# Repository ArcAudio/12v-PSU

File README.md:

# 12v-PSU
PSU

Use v2. Has correct cap traces.

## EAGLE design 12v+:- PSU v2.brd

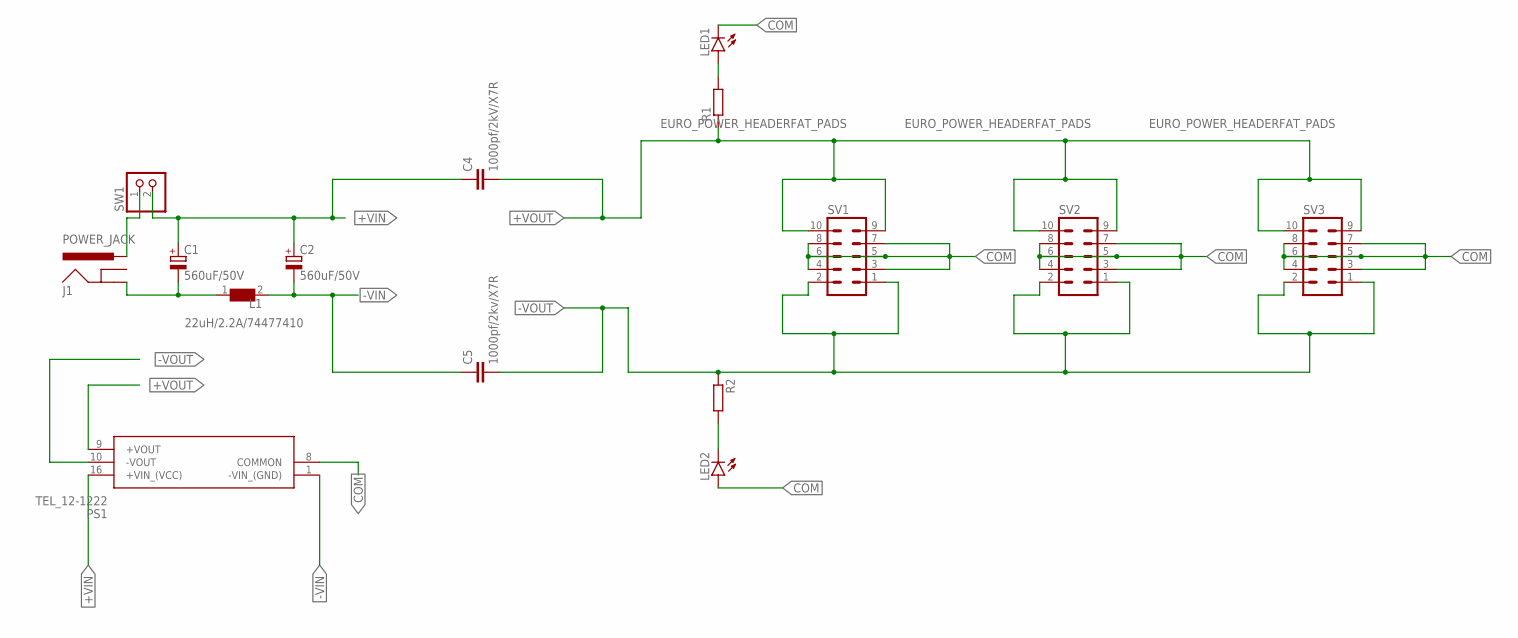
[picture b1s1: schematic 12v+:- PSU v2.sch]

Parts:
C1, C2: 560uF/50V; E7,5-16
C4: 1000pf/2kV/X7R; C1808
C5: 1000pf/2kv/X7R; C1808
J1: POWER_JACK; POWER_JACK_PTH
L1: 22uH/2.2A/74477410; WE-PD2_5848/5820
LED1, LED2: LED3MM
PS1: TEL_12-1222; TEL121222
R1, R2: RESISTOR7MM; 7MM_RESISTOR
SV1, SV2, SV3: EURO_POWER_HEADERFAT_PADS; EURO_PWR_HEADER_FAT
SW1: PINHD-1X2; 1X02

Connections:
+VIN: C1.+, C2.+, C4.1, PS1.16 (+VIN_(VCC)), SW1.2
+VOUT: C4.2, PS1.9 (+VOUT), R1.1, SV1.9, SV1.10, SV2.9, SV2.10, SV3.9, SV3.10
-VIN: C2.-, C5.1, L1.2, PS1.1 (-VIN_(GND))
-VOUT: C5.2, PS1.10 (-VOUT), R2.1, SV1.1, SV1.2, SV2.1, SV2.2, SV3.1, SV3.2
COM: LED1.K (C), LED2.A, PS1.8 (COMMON), SV1.3, SV1.4, SV1.5, SV1.6, SV1.7, SV1.8, SV2.3, SV2.4, SV2.5, SV2.6, SV2.7, SV2.8, SV3.3, SV3.4, SV3.5, SV3.6, SV3.7, SV3.8
unnamed: J1.PWR, SW1.1
unnamed: C1.-, J1.GND, L1.1
unnamed: LED1.A, R1.2
unnamed: LED2.K (C), R2.2

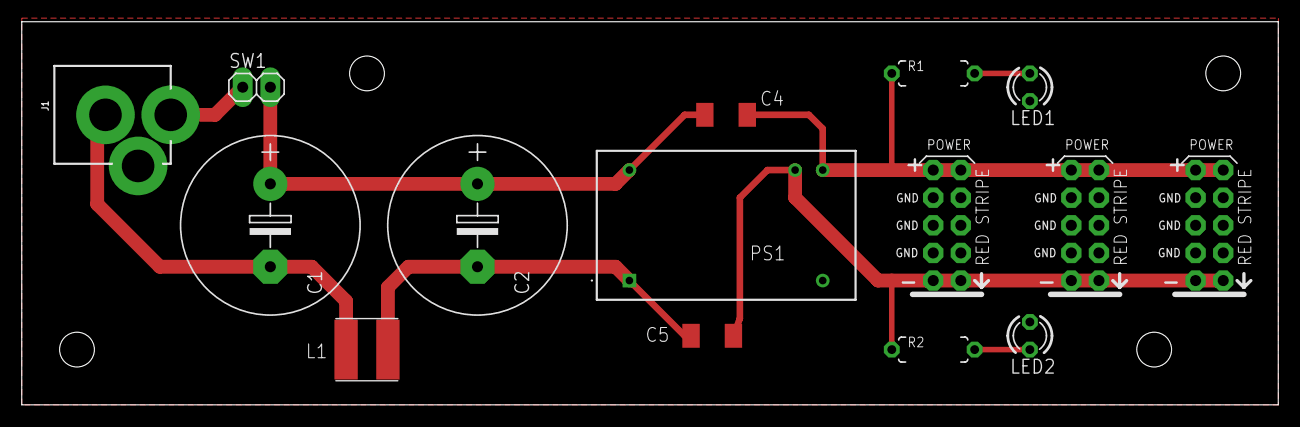
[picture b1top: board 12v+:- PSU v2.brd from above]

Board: 2 copper layers, 115.5 x 35.2 mm, 19 parts (0 on the bottom side), 9 nets.

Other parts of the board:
U$1, U$2, U$3, U$4: MOUNTING_HOLE

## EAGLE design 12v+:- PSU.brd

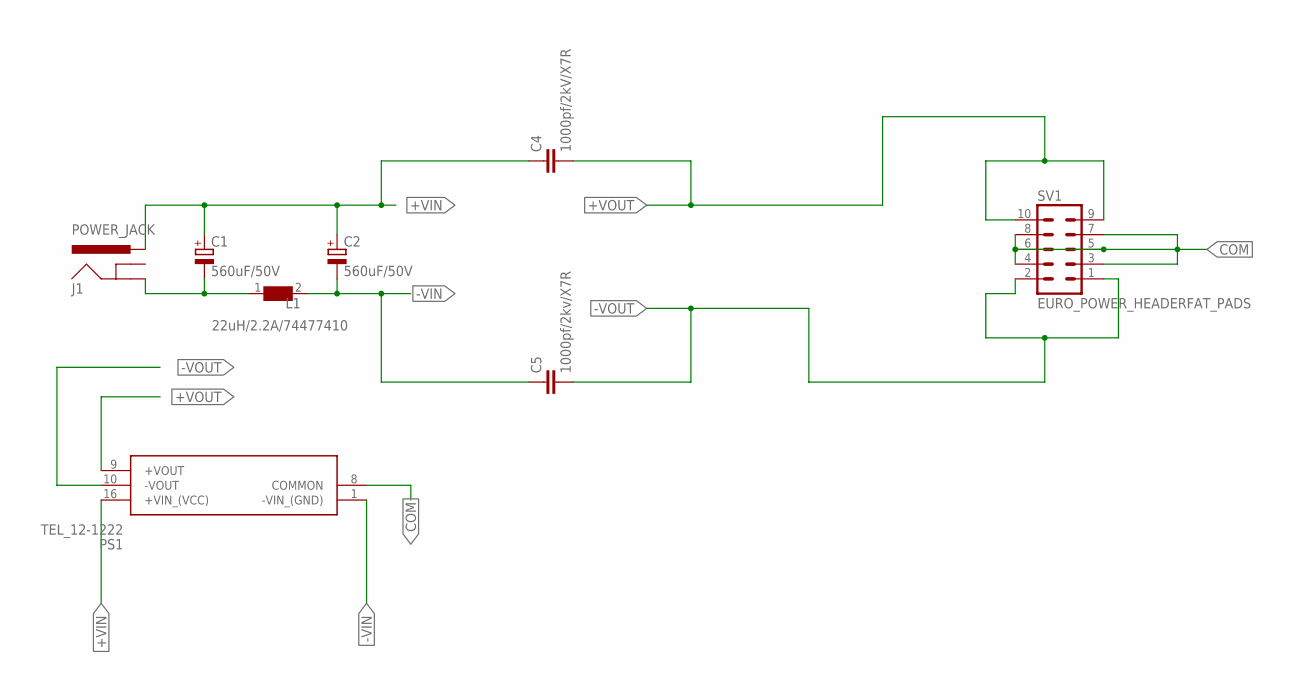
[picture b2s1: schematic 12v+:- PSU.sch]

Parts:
C1, C2: 560uF/50V; E7,5-16
C4: 1000pf/2kV/X7R; C0805
C5: 1000pf/2kv/X7R; C0805
J1: POWER_JACK; POWER_JACK_PTH
L1: 22uH/2.2A/74477410; WE-PD2_5848/5820
PS1: TEL_12-1222; TEL121222
SV1: EURO_POWER_HEADERFAT_PADS; EURO_PWR_HEADER_FAT

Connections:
+VIN: C1.+, C2.+, C4.1, J1.PWR, PS1.16 (+VIN_(VCC))
+VOUT: C4.2, PS1.9 (+VOUT), SV1.9, SV1.10
-VIN: C2.-, C5.1, L1.2, PS1.1 (-VIN_(GND))
-VOUT: C5.2, PS1.10 (-VOUT), SV1.1, SV1.2
COM: PS1.8 (COMMON), SV1.3, SV1.4, SV1.5, SV1.6, SV1.7, SV1.8
unnamed: C1.-, J1.GND, L1.1

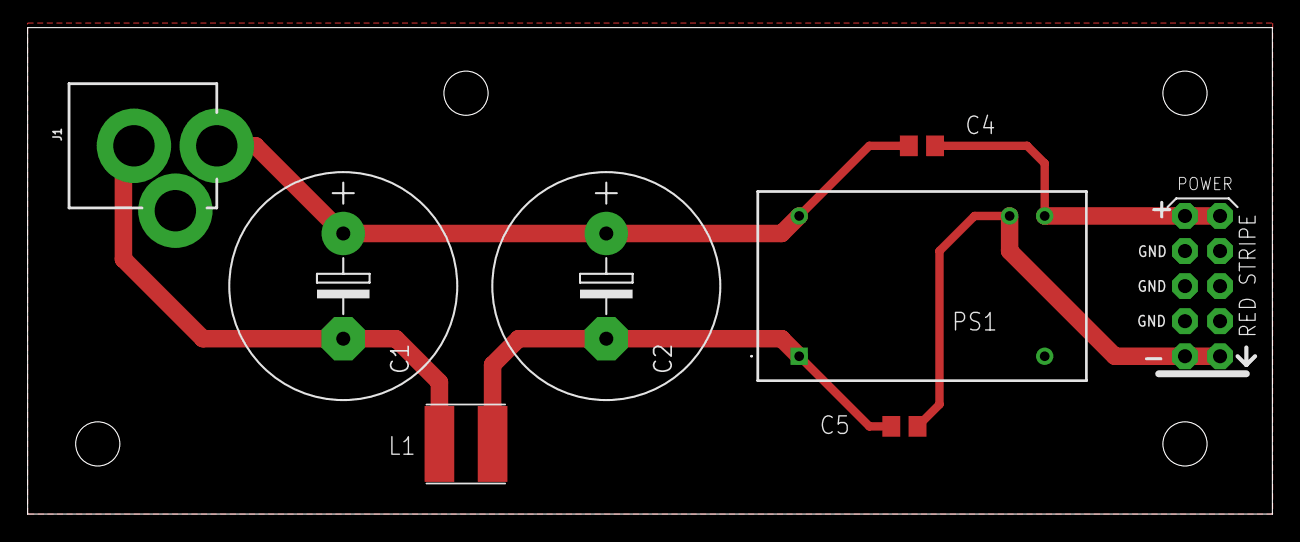
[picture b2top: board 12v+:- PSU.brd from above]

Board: 2 copper layers, 90.2 x 35.2 mm, 12 parts (0 on the bottom side), 6 nets.

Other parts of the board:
U$1, U$2, U$3, U$4: MOUNTING_HOLE

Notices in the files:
parts and their libraries:
SparkFun-Connectors: Licensing: Creative Commons ShareAlike 4.0 International - https://creativecommons.org/licenses/by-sa/4.0
